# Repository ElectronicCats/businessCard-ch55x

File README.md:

# Business Card

CH552 microcontroller with USB Business Card project established quite interesting circuit with very few elements. USB connector on the USB socket on the PCB designed to stop loose plaque thickness... Electronics Projects, USB Business Card with ch552, microcontroller projects

## License
Electronic Cats invests time and resources providing this open source design, please support Electronic Cats and open-source hardware by purchasing products from Electronic Cats!

Designed by Electronic Cats.

Firmware released under an GNU AGPL v3.0 license. See the LICENSE file for more information.

Hardware released under an CERN Open Hardware Licence v1.2. See the LICENSE_HARDWARE file for more information.

Electronic Cats is a registered trademark, please do not use if you sell these PCBs.

January 2020

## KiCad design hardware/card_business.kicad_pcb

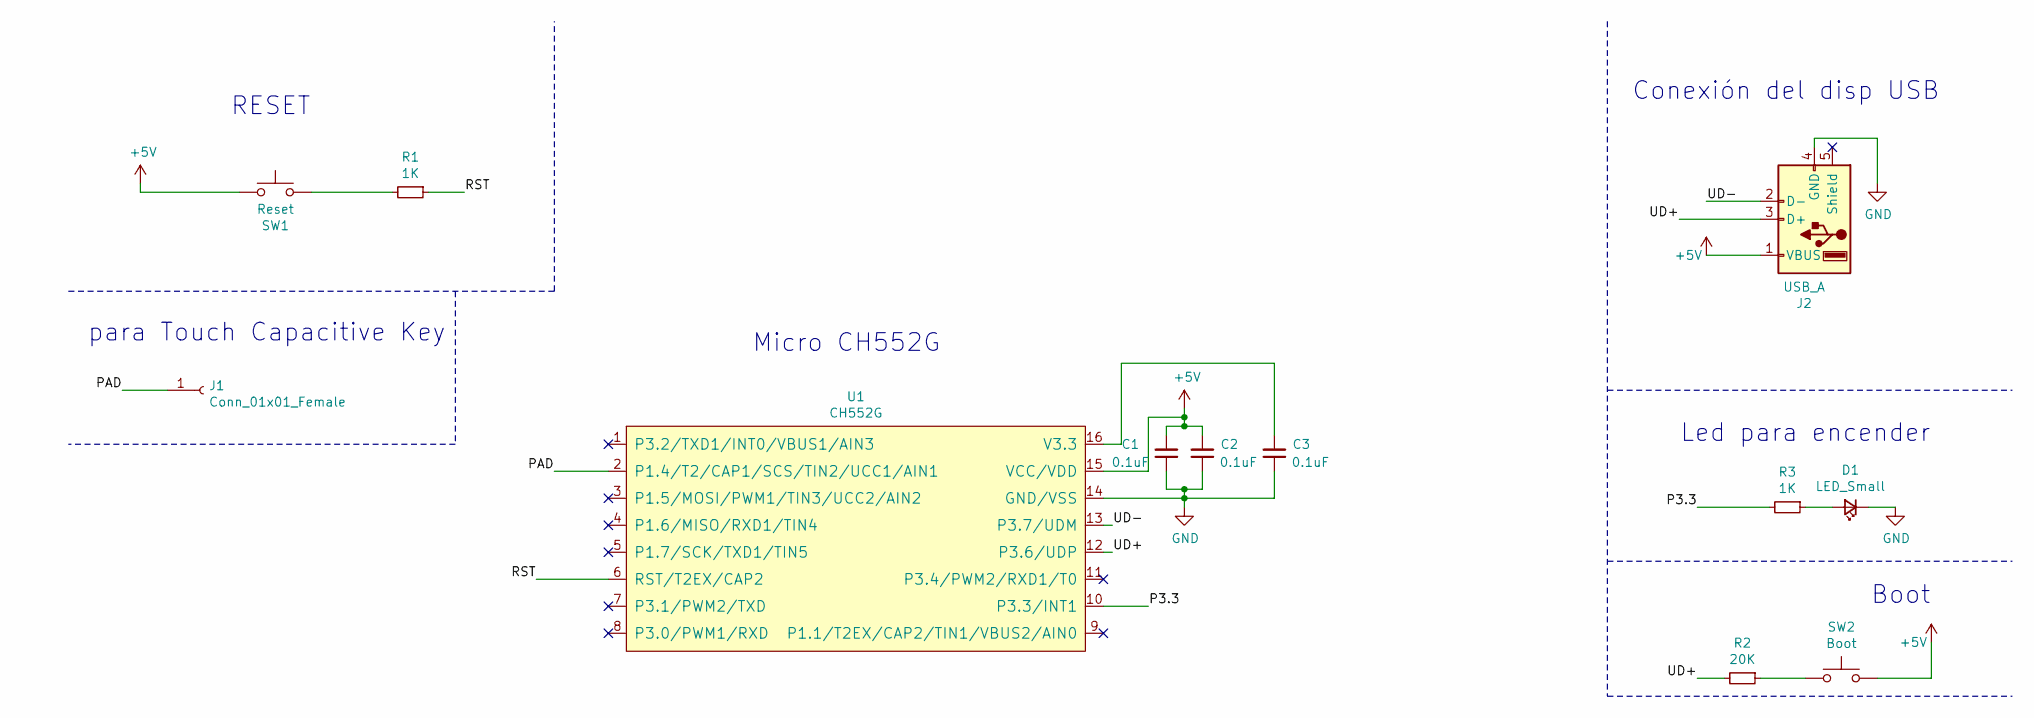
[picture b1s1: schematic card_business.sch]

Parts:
C1, C2, C3: 0.1uF; C_0805_2012Metric
D1: LED_Small; LED_0805_2012Metric
J1: Conn_01x01_Female; TestPoint_Pad_D4.0mm
J2: USB_A; usb-PCB
R1, R3: 1K; R_0805_2012Metric
R2: 20K; R_0805_2012Metric
SW1: Reset; SW_SPST_TL3342
SW2: Boot; SW_SPST_TL3342
U1: CH552G; SOP-16_4.55x10.3mm_P1.27mm

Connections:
+5V: C1.2, C2.2, J2.1 (VBUS), SW1.1, SW2.2, U1.15 (VCC/VDD)
/P3.3: R3.2, U1.10 (P3.3/INT1)
/PAD: J1.1, U1.2 (P1.4/T2/CAP1/SCS/TIN2/UCC1/AIN1)
/RST: R1.1, U1.6 (RST/T2EX/CAP2)
/UD+: J2.3 (D+), R2.2, U1.12 (P3.6/UDP)
/UD-: J2.2 (D-), U1.13 (P3.7/UDM)
GND: C1.1, C2.1, C3.1, D1.1 (K), J2.4 (GND), U1.14 (GND/VSS)
unnamed: C3.2, U1.16 (V3.3)
unnamed: D1.2 (A), R3.1
unnamed: R1.2, SW1.2
unnamed: R2.1, SW2.1

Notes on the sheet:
Conexión del disp USB
Led para encender
Micro CH552G
para Touch Capacitive Key
RESET
Boot

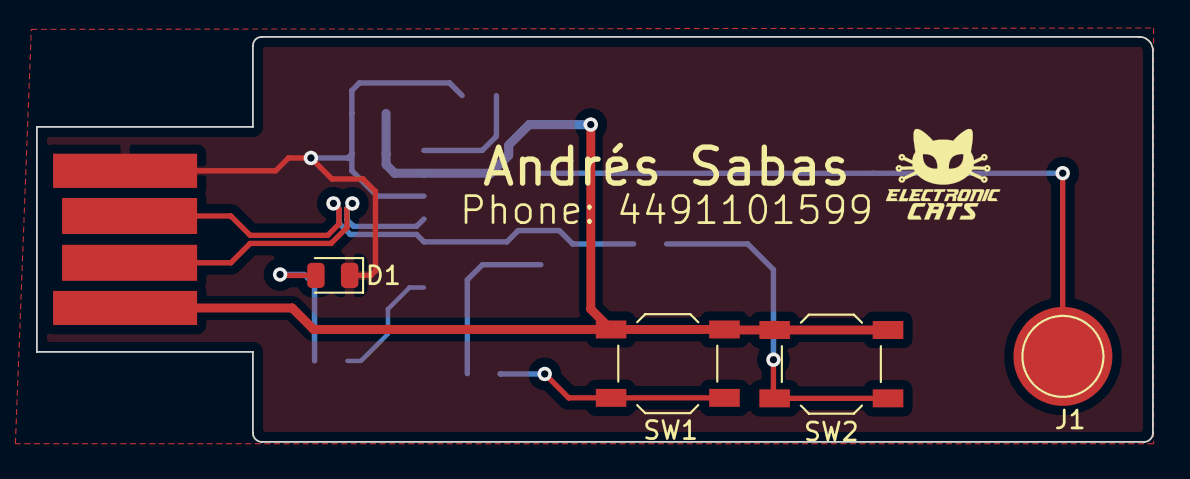
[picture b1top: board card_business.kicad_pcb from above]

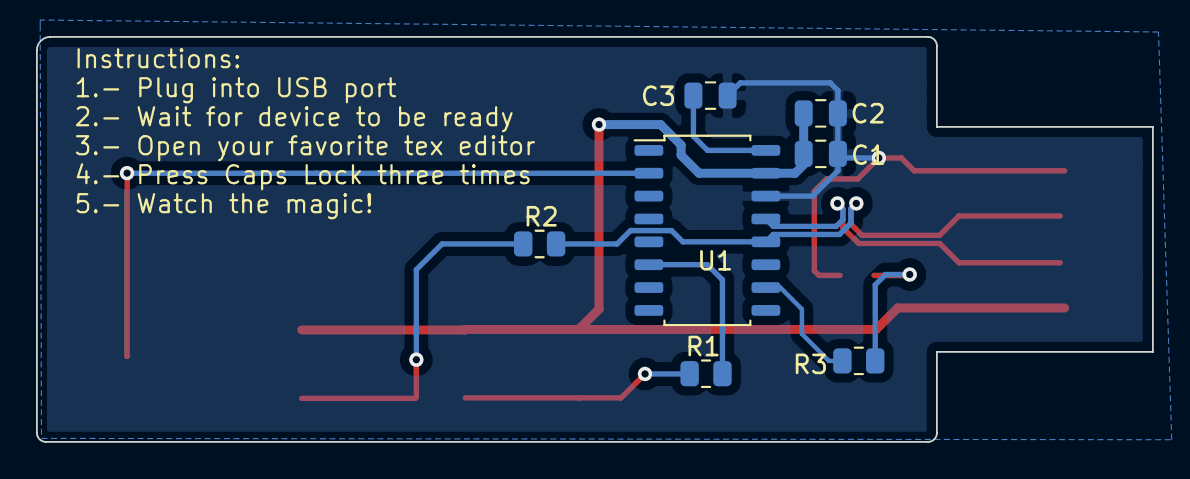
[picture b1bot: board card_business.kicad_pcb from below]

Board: 2 copper layers, 62.0 x 22.5 mm, 12 parts (7 on the bottom side), 11 nets.

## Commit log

2021-01-28 tarjeta_present
2021-01-28 Add ground template
2021-01-28 rename project and fix paths
2021-01-28 remove files
2021-01-29 routing complete
2021-01-29 add labels and logo
2021-01-29 side change
2021-01-29 labels
2021-01-29 change routing
2021-02-02 routing update
2021-02-02 routing update 2
2021-02-02 Change width of lines
2021-02-03 Change pin name and routing update
2021-02-03 update labels
2021-02-03 add back labels
2021-02-10 infocontactconstant
2021-02-10 ctrlledspanish
2021-02-11 TouchKeyLed
2021-02-17 add capacitor, modify traces
